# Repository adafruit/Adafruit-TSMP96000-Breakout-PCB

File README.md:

## Adafruit TSMP96000 "Code Learning" Infrared IR Receiver Breakout - STEMMA JST PH 2mm PCB

<a href="http://www.adafruit.com/products/5970"><br/>
Click here to purchase one from the Adafruit shop</a>

PCB files for the Adafruit TSMP96000 "Code Learning" Infrared IR Receiver Breakout - STEMMA JST PH 2mm. 

Format is EagleCAD schematic and board layout
* https://www.adafruit.com/product/5970

### Description

For classic 38KHz infrared remote signal reading, we've got a lovely STEMMA IR Receiver. But if you want to read infrared signals from remotes with different carrier signals, especially when you don't know the frequency, this Adafruit TSMP96000 "Code Learning" Infrared IR Receiver Breakout has the ability to detect IR signals from 20 to 60KHz and provide the carrier signal for analysis. This is used for "code learning" situations where you want your device to work with any IR remote control.

Usage is simple: Power the board by connecting V+ and ground to 3~5VDC, point a 20~60KHz IR remote control at the sensors, and press some buttons. The modulated IR signal, with the carrier signal intact, is piped out the Signal pin into your microcontroller which will then need to decode it. To make usage really easy, we have a green 'power good' LED and a red 'signal' LED. When IR remote signals are read by the onboard sensors, the red LED will blink to let you know.

This board will work nicely for advanced IR remote receiving projects, because you don't get the demodulated output it's not good for most IR decoding firmware - make sure you've got code specifically designed for "code learning"! With mounting holes and a cable, it's easy to mount in enclosures and on devices. Using a 2mm pitch STEMMA JST PH cable with headers or alligator clips on the end, you can easily wire this board without any soldering.

Each STEMMA board is a fully assembled and tested PCB, but no cable. No soldering is required to use it, but you will need to pick up a 2mm pitch, 3-pin STEMMA JST PH cable. Alternatively, if you do want to solder, there's a 0.1" spaced header for power/ground/signal.

### License

Adafruit invests time and resources providing this open source design, please support Adafruit and open-source hardware by purchasing products from [Adafruit](https://www.adafruit.com)!

Designed by Limor Fried/Ladyada for Adafruit Industries.

Creative Commons Attribution/Share-Alike, all text above must be included in any redistribution. 
See license.txt for additional details.

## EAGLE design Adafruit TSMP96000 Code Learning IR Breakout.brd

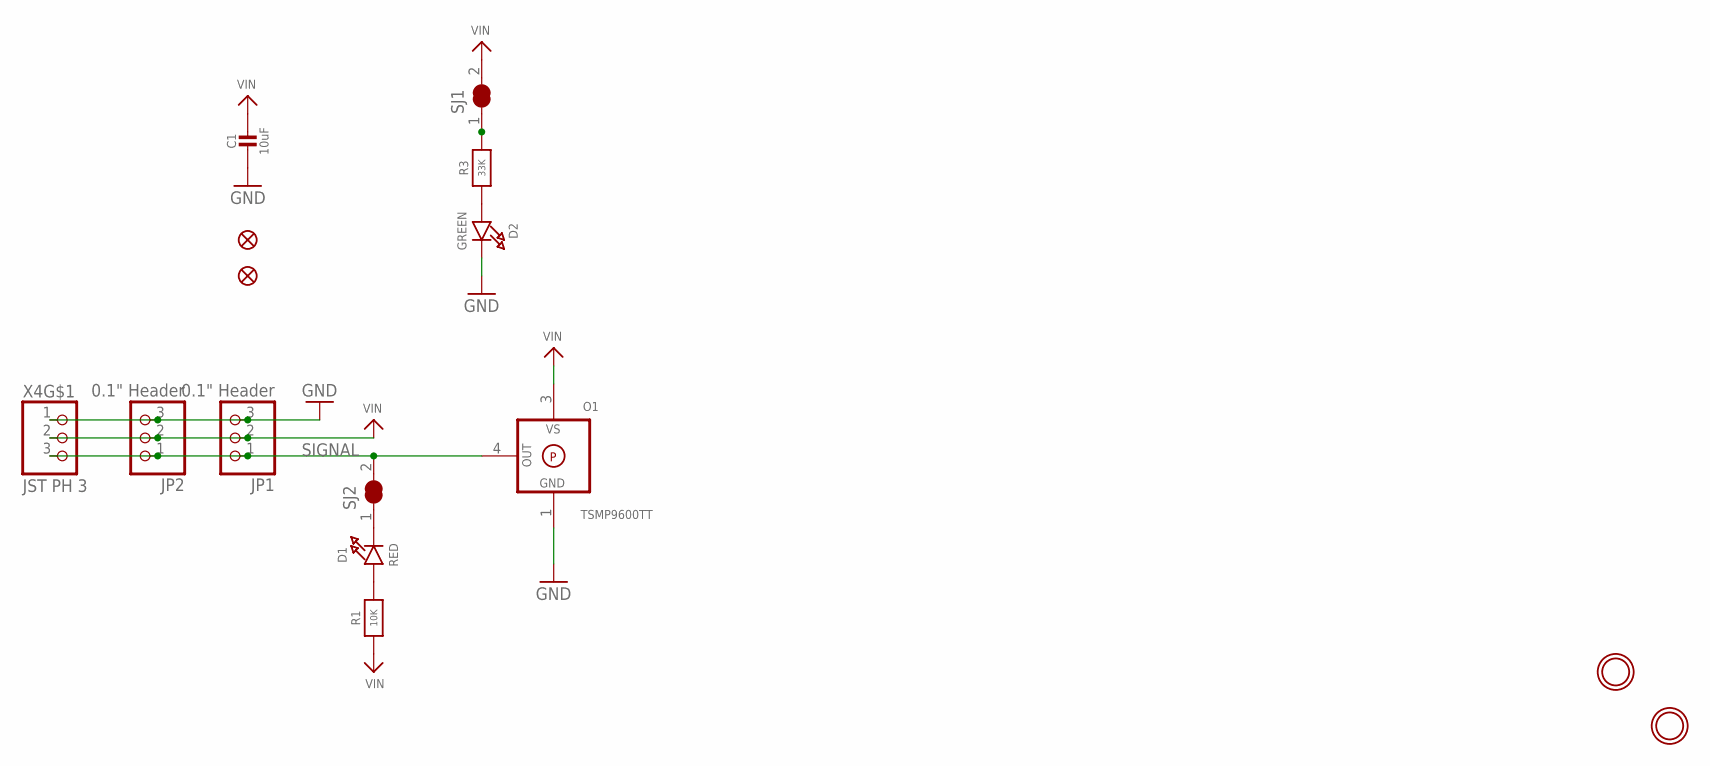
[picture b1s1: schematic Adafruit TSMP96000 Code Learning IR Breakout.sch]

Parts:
C1: 10uF; 0805-NO
D1: RED; CHIPLED_0603_NOOUTLINE
D2: GREEN; CHIPLED_0603_NOOUTLINE
FID2, FID3: FIDUCIAL_1MM
JP1: 0.1" Header; 1X03_OVAL
JP2: 0.1" Header; 1X03_ROUND_76
O1: TSMP9600TT; VISHAY_PANHEAD_TT
R1: 10K; 0603-NO
R3: 33K; 0603-NO
SJ1, SJ2: SOLDERJUMPER_CLOSED; SOLDERJUMPER_CLOSEDWIRE
U$1, U$8: MOUNTINGHOLE2.5; MOUNTINGHOLE_2.5_PLATED
X4: JST PH 3; JSTPH3

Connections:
GND: C1.2, D2.C, JP1.3, JP2.3, O1.1 (GND), X4.1
unnamed: R3.2, SJ1.1
unnamed: D1.C, SJ2.1
unnamed: D1.A, R1.2
unnamed: D2.A, R3.1
SIGNAL: JP1.1, JP2.1, O1.4 (OUT), SJ2.2, X4.3
VIN: C1.1, JP1.2, JP2.2, O1.3 (VS), R1.1, SJ1.2, X4.2

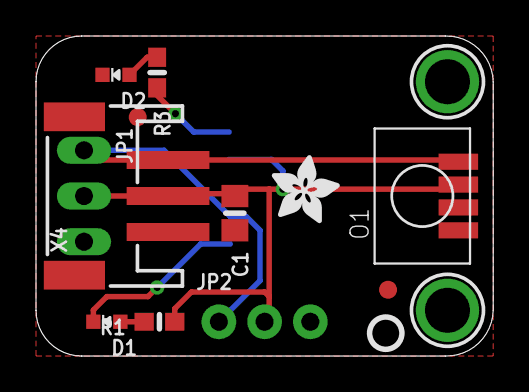
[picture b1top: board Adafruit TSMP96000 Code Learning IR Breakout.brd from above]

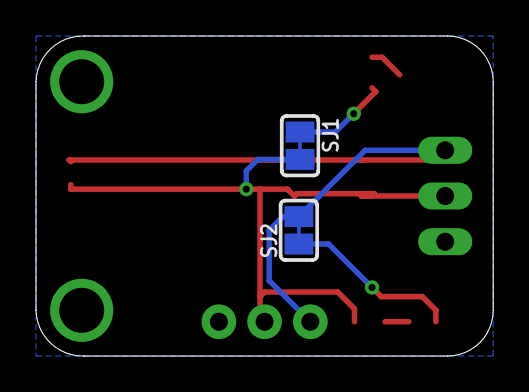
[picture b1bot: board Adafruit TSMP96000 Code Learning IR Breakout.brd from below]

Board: 2 copper layers, 25.4 x 17.8 mm, 33 parts (12 on the bottom side), 7 nets.

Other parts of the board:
PLABEL0: PLABEL0
PLABEL1: PLABEL1
PLABEL2, PLABEL14: PLABEL14
PLABEL3, PLABEL13: PLABEL13
PLABEL4, PLABEL20: PLABEL20
PLABEL5: PLABEL5
PLABEL6: PLABEL6
PLABEL10: PLABEL10
PLABEL16: PLABEL16
PLABEL17: PLABEL17
PLABEL18: PLABEL18
PLABEL21: PLABEL21
PLABEL22: PLABEL22
U$5: PCBFEAT-REV-040
U$10: ADAFRUIT_3.5MM

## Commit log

2024-06-04 cookiecutter

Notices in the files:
parts and their libraries:
microbuilder: This work is placed in the public domain, and may be freely used for commercial and non-commercial work with the following conditions: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
